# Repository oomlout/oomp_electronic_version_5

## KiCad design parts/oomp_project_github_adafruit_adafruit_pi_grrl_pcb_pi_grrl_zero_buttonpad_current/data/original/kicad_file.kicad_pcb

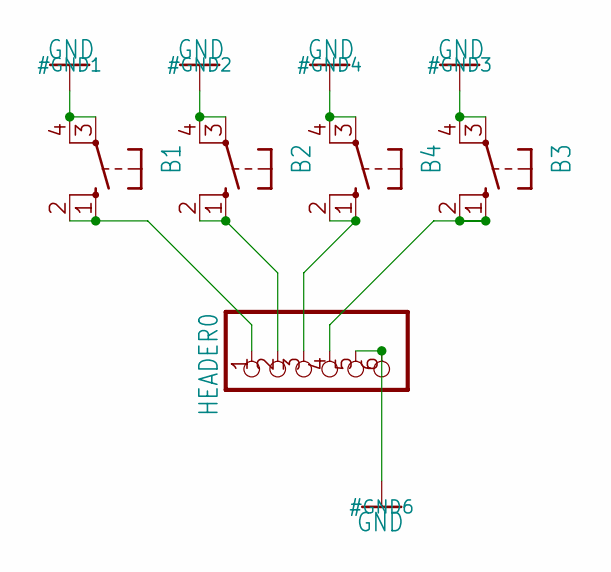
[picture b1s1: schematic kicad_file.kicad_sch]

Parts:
B1, B2, B3, B4: 10-XX; B3F-10XX; MPN B3F-1000
HEADER0: PINHD-1X6; 1X06

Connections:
GND: B1.3, B1.4 (P1), B2.3, B2.4 (P1), B3.3, B3.4 (P1), B4.3, B4.4 (P1), HEADER0.5, HEADER0.6
unnamed: B1.1 (S), B1.2 (S1), HEADER0.1
unnamed: B2.1 (S), B2.2 (S1), HEADER0.2
unnamed: B3.1 (S), B3.2 (S1), HEADER0.4
unnamed: B4.1 (S), B4.2 (S1), HEADER0.3

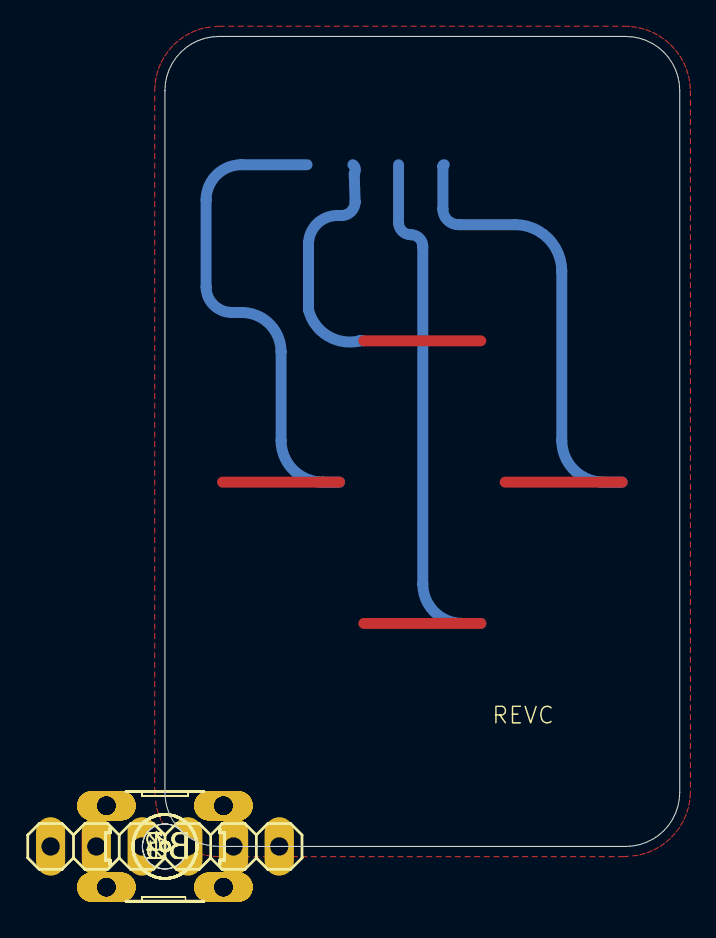
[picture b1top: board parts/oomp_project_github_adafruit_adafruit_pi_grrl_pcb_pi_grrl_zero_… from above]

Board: 16 copper layers, 28.6 x 45.0 mm, 7 parts (0 on the bottom side), 5 nets.

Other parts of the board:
UNK_HOLE_0: dummyfp0
UNK_HOLE_1: dummyfp1

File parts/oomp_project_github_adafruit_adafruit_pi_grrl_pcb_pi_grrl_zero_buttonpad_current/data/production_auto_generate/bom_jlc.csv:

Comment,Designator,Footprint,LCSC Part #
,HEADER0,PiGRRL_Zero_buttonpad-import-fps:1X06,C37208
,"B1,B2,B3,B4",PiGRRL_Zero_buttonpad-import-fps:B3F-10XX,

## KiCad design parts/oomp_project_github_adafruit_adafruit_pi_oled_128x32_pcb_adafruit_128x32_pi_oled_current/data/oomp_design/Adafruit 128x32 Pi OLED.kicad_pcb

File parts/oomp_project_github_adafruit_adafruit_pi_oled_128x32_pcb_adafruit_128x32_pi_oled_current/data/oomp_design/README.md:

# OOMP KiCad design copy

Open `Adafruit 128x32 Pi OLED.kicad_pro` (or the `.kicad_pcb` / `.kicad_sch`) in KiCad. Local OOMP libraries are under `libraries/`. Original inputs are preserved in [../original/](../original/).

Only verified unchanged installed KiCad defaults were renamed. Modified, custom, unmatched and unavailable items remain unchanged. Soldering variants are never swapped during conversion. Existing pad coordinates, nets and UUIDs are preserved.

See [conversion_report.yaml](conversion_report.yaml) for every conversion and skip. Copy this directory before editing; regeneration refuses to overwrite edited design files.

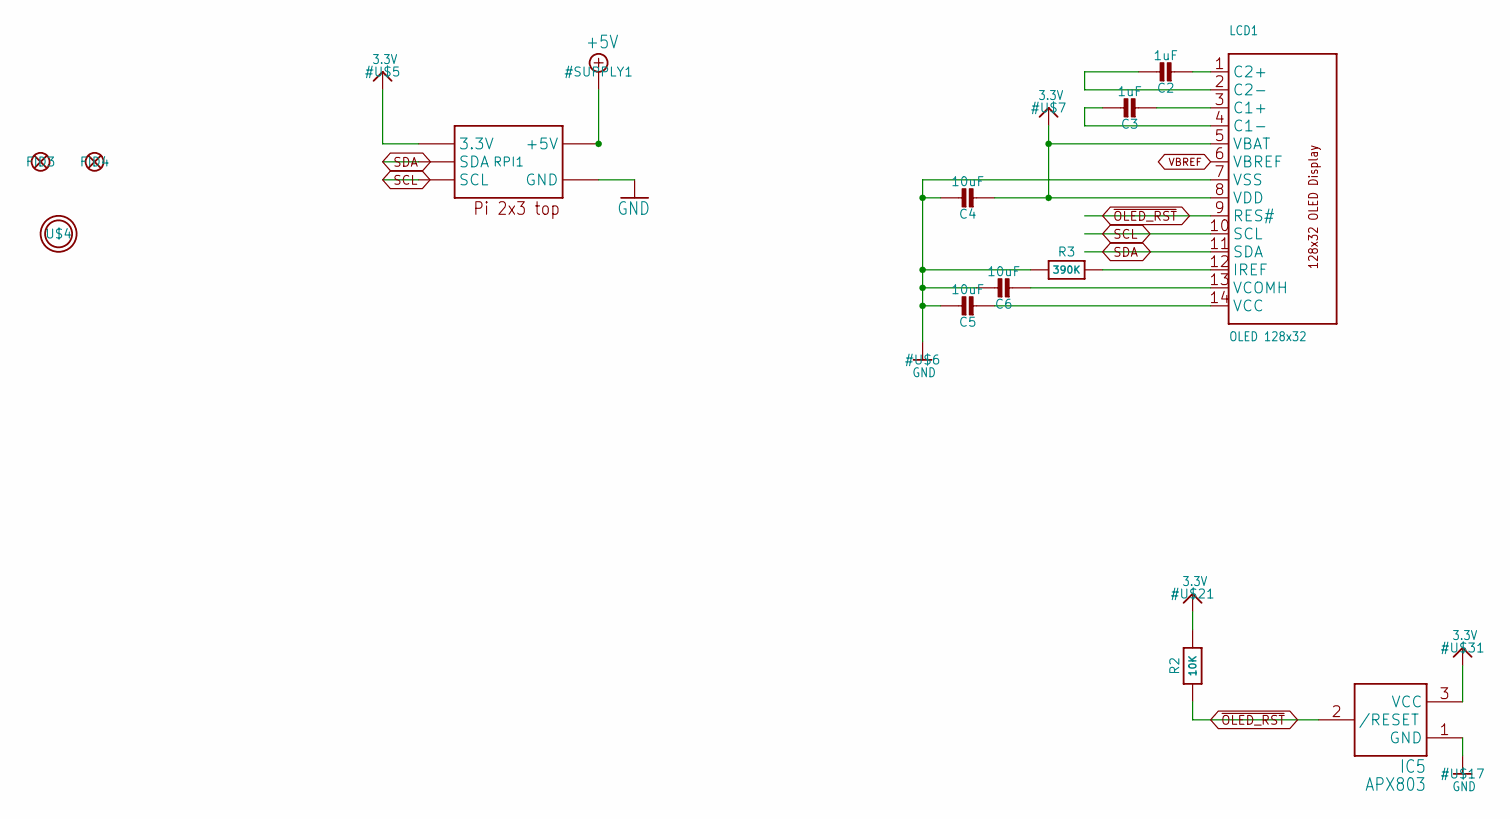
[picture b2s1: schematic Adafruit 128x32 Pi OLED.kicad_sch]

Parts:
C2, C3: 1uF; 0805-NO
C4, C5, C6: 10uF; 0805-NO
FID3, FID4: FIDUCIAL_1MM
IC5: APX803; SOT23
LCD1: OLED 128x32; UG-2832HSWEG02_WRAPUNDER
R2: 10K; 0805-NO
R3: 390K; 0805-NO
RPI1: RASPBERRYPI_2X3; RASPBERRYPI_2X3_THMSMT
U$4: MOUNTINGHOLE3.0THIN; MOUNTINGHOLE_3.0_PLATEDTHIN

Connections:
3.3V: C4.2, IC5.3 (VCC), LCD1.5 (VBAT), LCD1.8 (VDD), R2.2, RPI1.1 (3.3V), RPI1.1' (3.3V)
+5V: RPI1.2 (+5V), RPI1.2' (+5V), RPI1.4 (+5V), RPI1.4' (+5V)
GND: C4.1, C5.1, C6.1, IC5.1 (GND), LCD1.7 (VSS), R3.1, RPI1.6 (GND), RPI1.6' (GND)
unnamed: C2.2, LCD1.1 (C2+)
unnamed: C2.1, LCD1.2 (C2-)
unnamed: C3.2, LCD1.3 (C1+)
unnamed: C3.1, LCD1.4 (C1-)
unnamed: C6.2, LCD1.13 (VCOMH)
unnamed: C5.2, LCD1.14 (VCC)
unnamed: LCD1.12 (IREF), R3.2
SCL: LCD1.10 (SCL), RPI1.5 (SCL), RPI1.5' (SCL)
SDA: LCD1.11 (SDA), RPI1.3 (SDA), RPI1.3' (SDA)
VBREF: LCD1.6 (VBREF)
~OLED_RST: IC5.2 (/RESET), LCD1.9 (RES#), R2.1

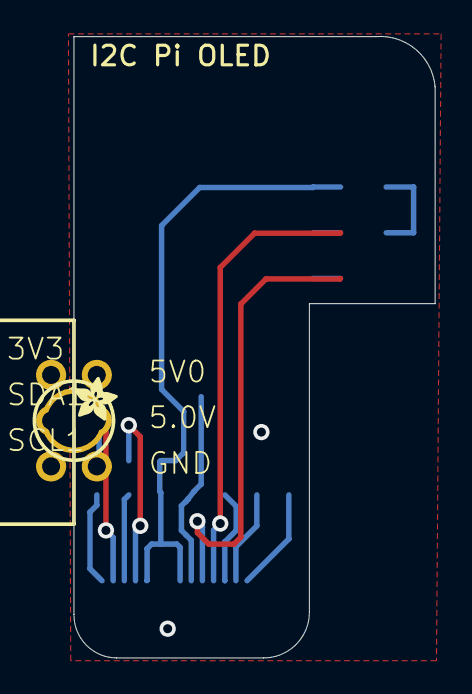
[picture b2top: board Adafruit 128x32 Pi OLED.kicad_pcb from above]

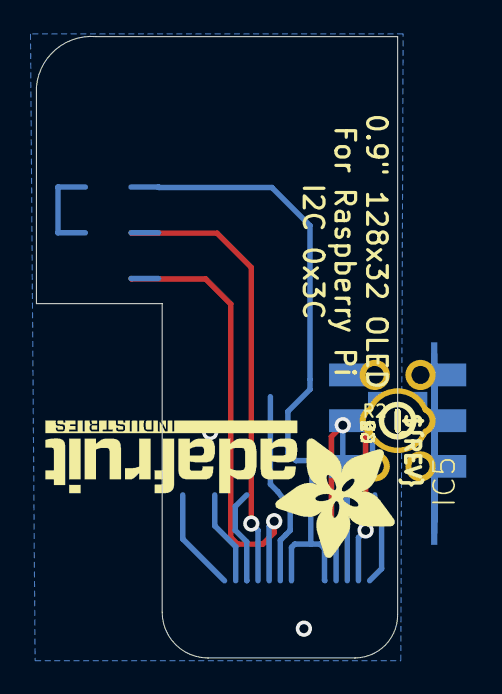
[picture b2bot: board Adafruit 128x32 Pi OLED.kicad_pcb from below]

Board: 16 copper layers, 20.1 x 34.5 mm, 16 parts (12 on the bottom side), 13 nets.

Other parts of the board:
U$1: ADAFRUIT_2.5MM
U$3: PCBFEAT-REV-040
U$8: ADAFRUIT_TEXT_20MM

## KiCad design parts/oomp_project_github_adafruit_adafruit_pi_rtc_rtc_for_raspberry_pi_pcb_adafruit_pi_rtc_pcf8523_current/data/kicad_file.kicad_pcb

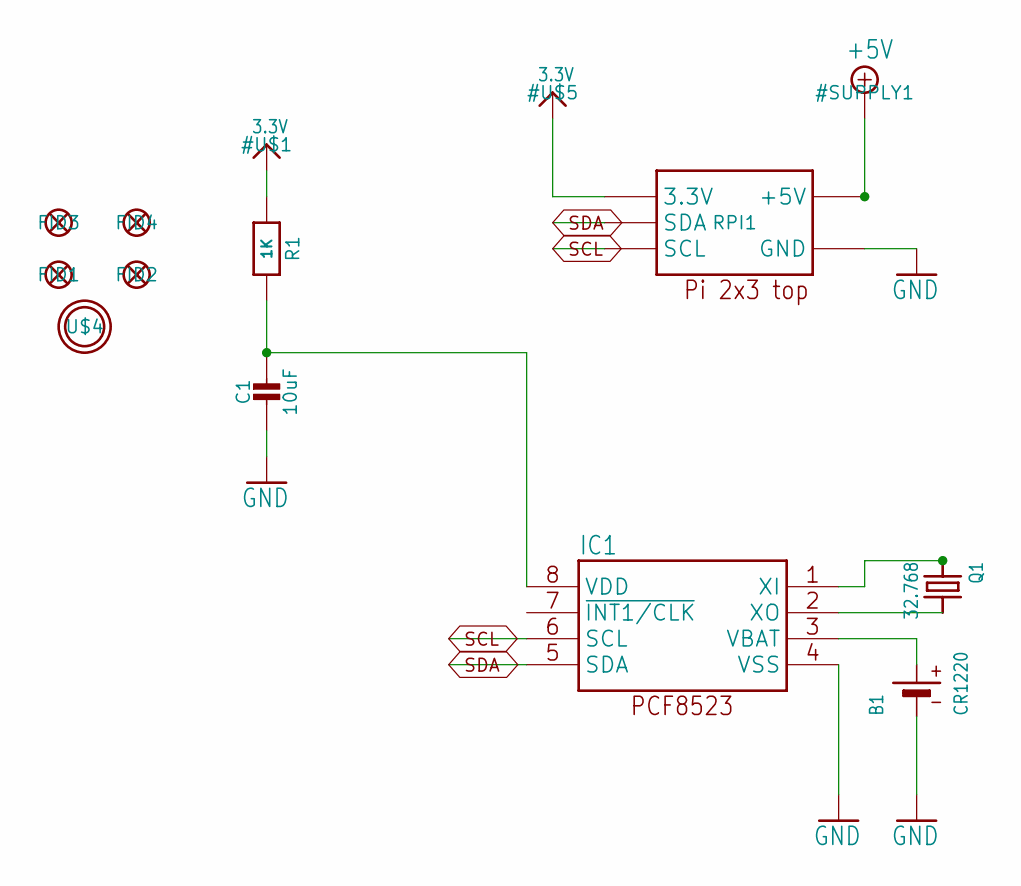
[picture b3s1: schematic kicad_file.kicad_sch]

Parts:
B1: CR1220
C1: 10uF; 0805-NO
FID1, FID2, FID3, FID4: FIDUCIAL_1MM
IC1: RTC_PCF8523T; SOIC8_150MIL
Q1: 32.768; CRYSTAL_8X3.8
R1: 1K; 0805-NO
RPI1: RASPBERRYPI_2X3; RASPBERRYPI_2X3_THMSMT
U$4: MOUNTINGHOLE3.0THIN; MOUNTINGHOLE_3.0_PLATEDTHIN

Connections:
3.3V: R1.1, RPI1.1 (3.3V), RPI1.1' (3.3V)
+5V: RPI1.2 (+5V), RPI1.2' (+5V), RPI1.4 (+5V), RPI1.4' (+5V)
GND: B1.-, C1.2, IC1.4 (VSS), RPI1.6 (GND), RPI1.6' (GND)
unnamed: IC1.1 (XI), Q1.P$1 (1)
unnamed: IC1.2 (XO), Q1.P$4 (2)
SCL: IC1.6 (SCL), RPI1.5 (SCL), RPI1.5' (SCL)
SDA: IC1.5 (SDA), RPI1.3 (SDA), RPI1.3' (SDA)
VBAT: B1.+$1 (+), B1.+$2 (+), IC1.3 (VBAT)
VDD: C1.1, IC1.8 (VDD), R1.2

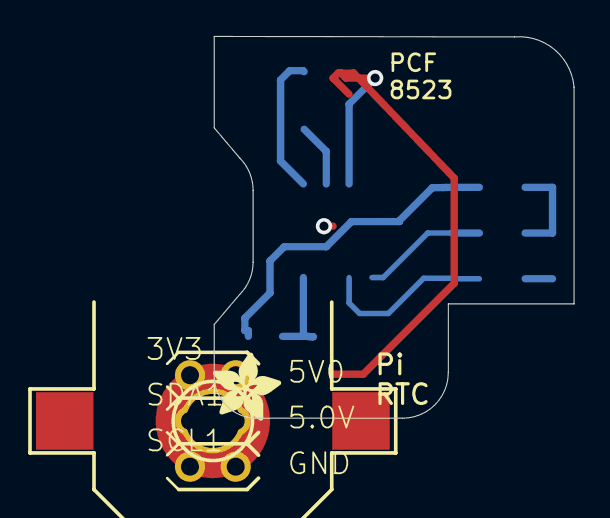
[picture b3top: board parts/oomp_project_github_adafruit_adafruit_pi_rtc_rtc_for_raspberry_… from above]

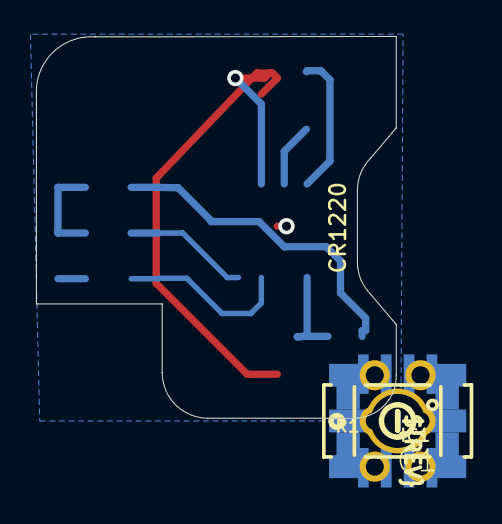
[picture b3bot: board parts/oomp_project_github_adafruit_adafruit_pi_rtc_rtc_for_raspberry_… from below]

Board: 16 copper layers, 20.0 x 21.2 mm, 13 parts (7 on the bottom side), 9 nets.

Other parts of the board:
U$2: ADAFRUIT_3.5MM
U$3: PCBFEAT-REV-040

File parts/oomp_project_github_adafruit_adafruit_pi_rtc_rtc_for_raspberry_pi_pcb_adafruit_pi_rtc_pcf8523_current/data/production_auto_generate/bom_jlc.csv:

Comment,Designator,Footprint,LCSC Part #
,U$2,Adafruit PiRTC PCF8523-import-fps:ADAFRUIT_3.5MM,
,U$3,Adafruit PiRTC PCF8523-import-fps:PCBFEAT-REV-040,
10uF,C1,Adafruit PiRTC PCF8523-import-fps:0805-NO,
1K,R1,Adafruit PiRTC PCF8523-import-fps:0805-NO,C17513
32.768,Q1,Adafruit PiRTC PCF8523-import-fps:CRYSTAL_8X3.8,
CR1220,B1,Adafruit PiRTC PCF8523-import-fps:CR1220,
RASPBERRYPI_2X3,RPI1,Adafruit PiRTC PCF8523-import-fps:RASPBERRYPI_2X3_THMSMT,
RTC_PCF8523T,IC1,Adafruit PiRTC PCF8523-import-fps:SOIC8_150MIL,

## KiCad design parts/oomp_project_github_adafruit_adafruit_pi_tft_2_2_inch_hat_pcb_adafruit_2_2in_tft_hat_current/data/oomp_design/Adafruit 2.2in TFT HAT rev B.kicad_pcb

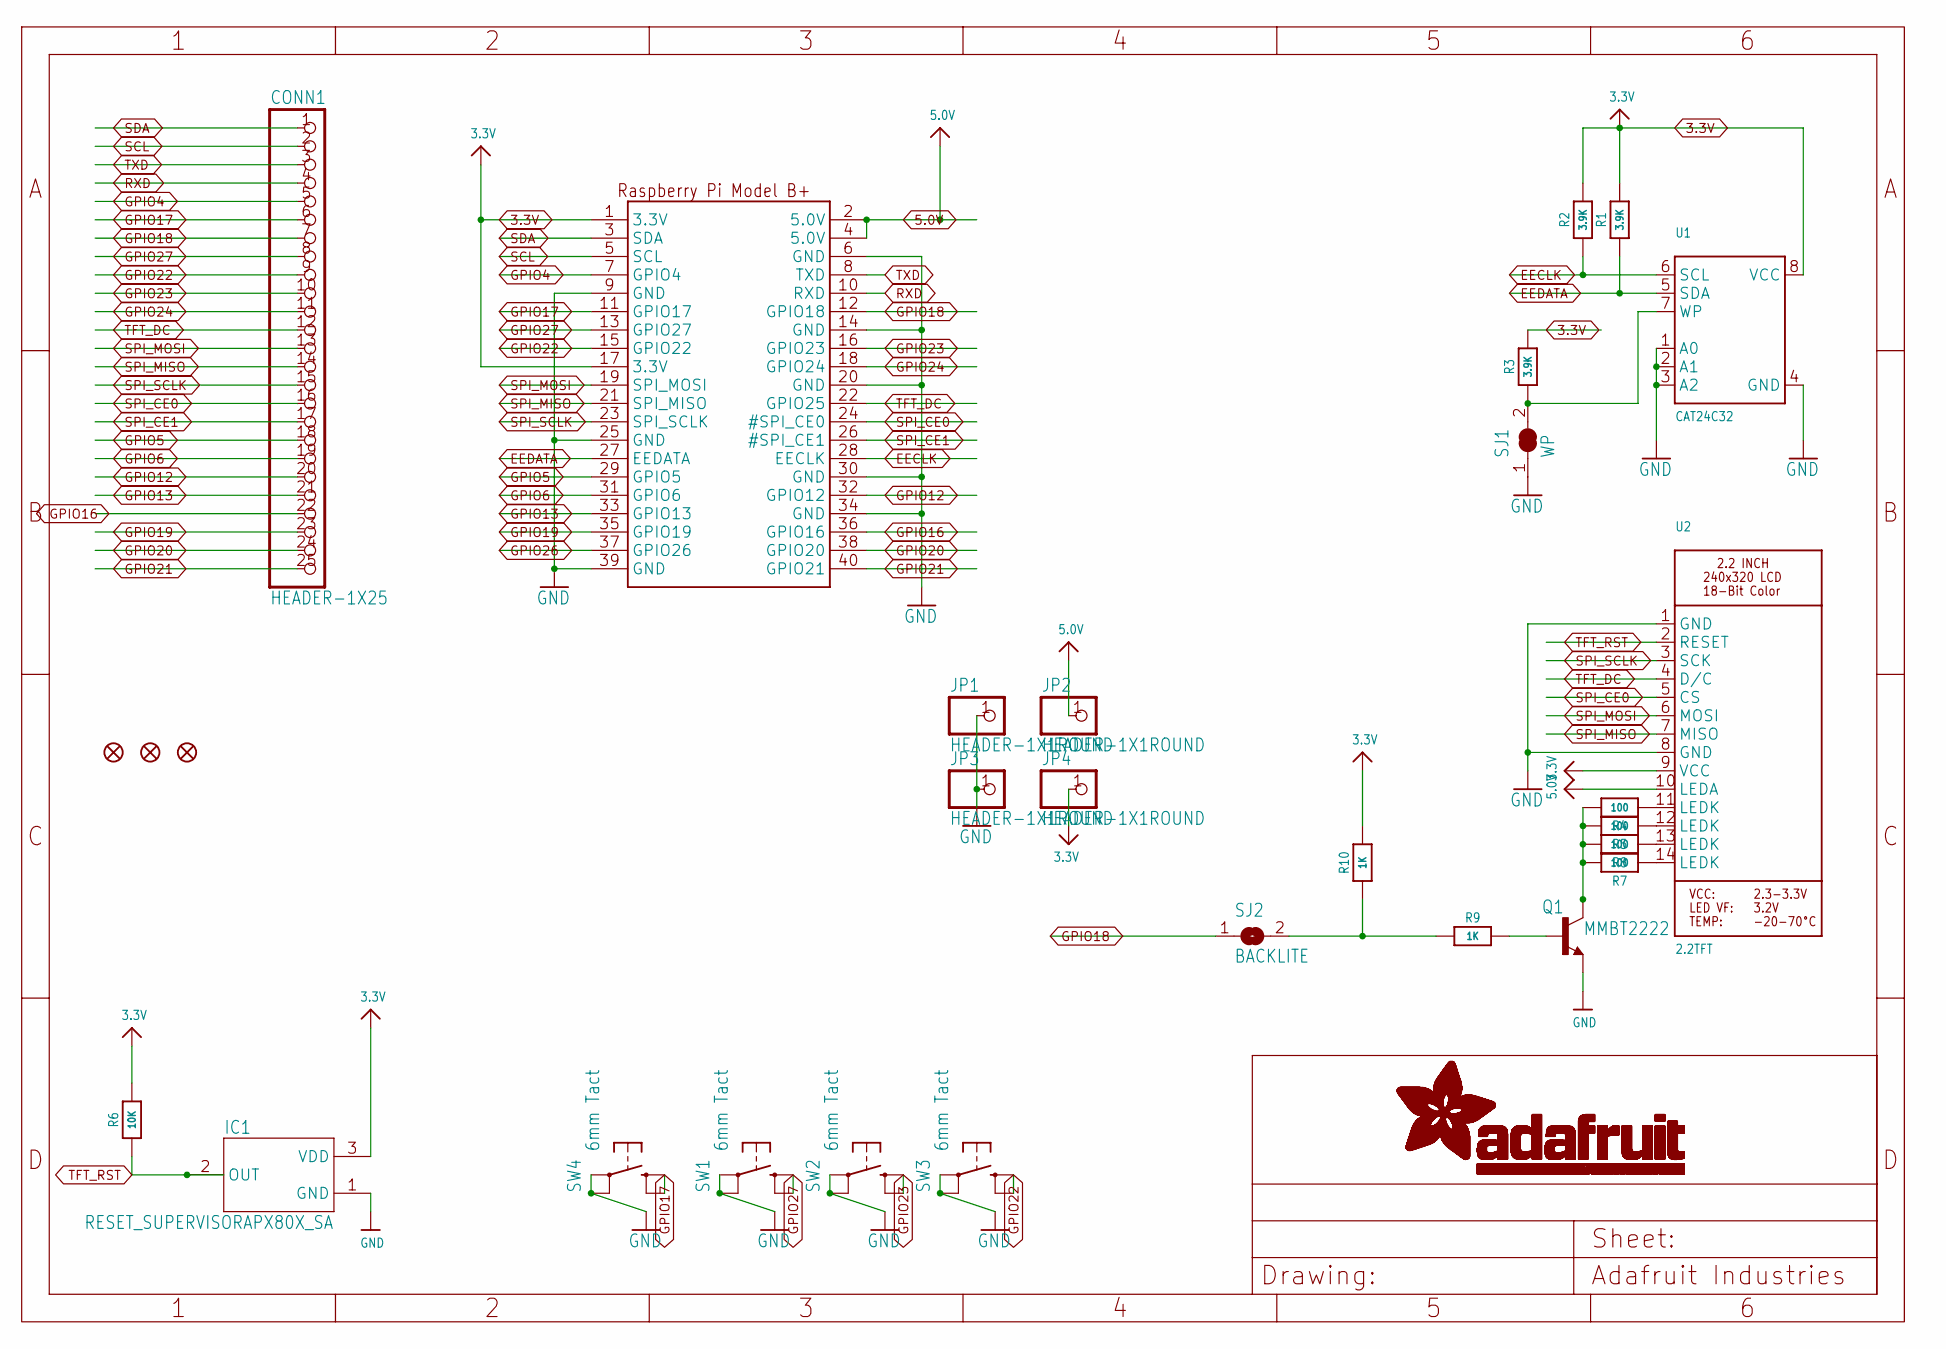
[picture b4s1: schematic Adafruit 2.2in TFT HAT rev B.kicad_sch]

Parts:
CONN1: HEADER-1X25; 1X25_ROUND_70MIL
FID1, FID2, FID3: FIDUCIAL_1MM
IC1: RESET_SUPERVISORAPX80X_SA; SOT23-WIDE
JP1, JP2, JP3, JP4: HEADER-1X1ROUND; 1X01_ROUND
Q1: MMBT2222; SOT23-BEC
R1, R2, R3: 3.9K; 0805-NO
R4, R5, R7, R8: 100; 0805-NO
R6: 10K; 0805-NO
R9, R10: 1K; 0805-NO
RPI1: RASPBERRYPI_BPLUS_HATNODIM; PI_HAT_NODIM
SJ1: WP; SOLDERJUMPER_CLOSEDWIRE
SJ2: BACKLITE; SOLDERJUMPER_CLOSEDWIRE
SW1, SW2, SW3, SW4: 6mm Tact; EVQ-Q2
U1: CAT24C32; SOIC8_150MIL
U2: 2.2TFT; TM022HDH26_2.2IN_LCD

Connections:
3.3V: IC1.3 (VDD), JP4.1, R1.2, R2.2, R3.2, R6.2, R10.2, RPI1.1 (3.3V), RPI1.17 (3.3V), U1.8 (VCC), U2.9 (VCC)
5.0V: JP2.1, RPI1.2 (5.0V), RPI1.4 (5.0V), U2.10 (LEDA)
EECLK: R2.1, RPI1.28 (EECLK), U1.6 (SCL)
EEDATA: R1.1, RPI1.27 (EEDATA), U1.5 (SDA)
GND: IC1.1 (GND), JP1.1, JP3.1, Q1.E, RPI1.6 (GND), RPI1.9 (GND), RPI1.14 (GND), RPI1.20 (GND), RPI1.25 (GND), RPI1.30 (GND), RPI1.34 (GND), RPI1.39 (GND), SJ1.1, SW1.A, SW1.A' (P1), SW2.A, SW2.A' (P1), SW3.A, SW3.A' (P1), SW4.A, SW4.A' (P1), U1.1 (A0), U1.2 (A1), U1.3 (A2), U1.4 (GND), U2.1 (GND), U2.8 (GND)
GPIO4: CONN1.5, RPI1.7 (GPIO4)
GPIO5: CONN1.18, RPI1.29 (GPIO5)
GPIO6: CONN1.19, RPI1.31 (GPIO6)
GPIO12: CONN1.20, RPI1.32 (GPIO12)
GPIO13: CONN1.21, RPI1.33 (GPIO13)
GPIO16: CONN1.22, RPI1.36 (GPIO16)
GPIO17: CONN1.6, RPI1.11 (GPIO17), SW4.B (S), SW4.B' (S1)
GPIO18: CONN1.7, RPI1.12 (GPIO18), SJ2.1
GPIO19: CONN1.23, RPI1.35 (GPIO19)
GPIO20: CONN1.24, RPI1.38 (GPIO20)
GPIO21: CONN1.25, RPI1.40 (GPIO21)
GPIO22: CONN1.9, RPI1.15 (GPIO22), SW3.B (S), SW3.B' (S1)
GPIO23: CONN1.10, RPI1.16 (GPIO23), SW2.B (S), SW2.B' (S1)
GPIO24: CONN1.11, RPI1.18 (GPIO24)
GPIO26: RPI1.37 (GPIO26)
GPIO27: CONN1.8, RPI1.13 (GPIO27), SW1.B (S), SW1.B' (S1)
unnamed: R4.1, U2.11 (LEDK)
unnamed: R5.1, U2.12 (LEDK)
unnamed: R7.1, U2.14 (LEDK)
unnamed: R8.1, U2.13 (LEDK)
unnamed: Q1.C, R4.2, R5.2, R7.2, R8.2
unnamed: Q1.B, R9.2
unnamed: R9.1, R10.1, SJ2.2
unnamed: R3.1, SJ1.2, U1.7 (WP)
RXD: CONN1.4, RPI1.10 (RXD)
SCL: CONN1.2, RPI1.5 (SCL)
SDA: CONN1.1, RPI1.3 (SDA)
SPI_CE0: CONN1.16, RPI1.24 (#SPI_CE0), U2.5 (CS)
SPI_CE1: CONN1.17, RPI1.26 (#SPI_CE1)
SPI_MISO: CONN1.14, RPI1.21 (SPI_MISO), U2.7 (MISO)
SPI_MOSI: CONN1.13, RPI1.19 (SPI_MOSI), U2.6 (MOSI)
SPI_SCLK: CONN1.15, RPI1.23 (SPI_SCLK), U2.3 (SCK)
TFT_DC: CONN1.12, RPI1.22 (GPIO25), U2.4 (D/C)
TFT_RST: IC1.2 (OUT), R6.1, U2.2 (RESET)
TXD: CONN1.3, RPI1.8 (TXD)

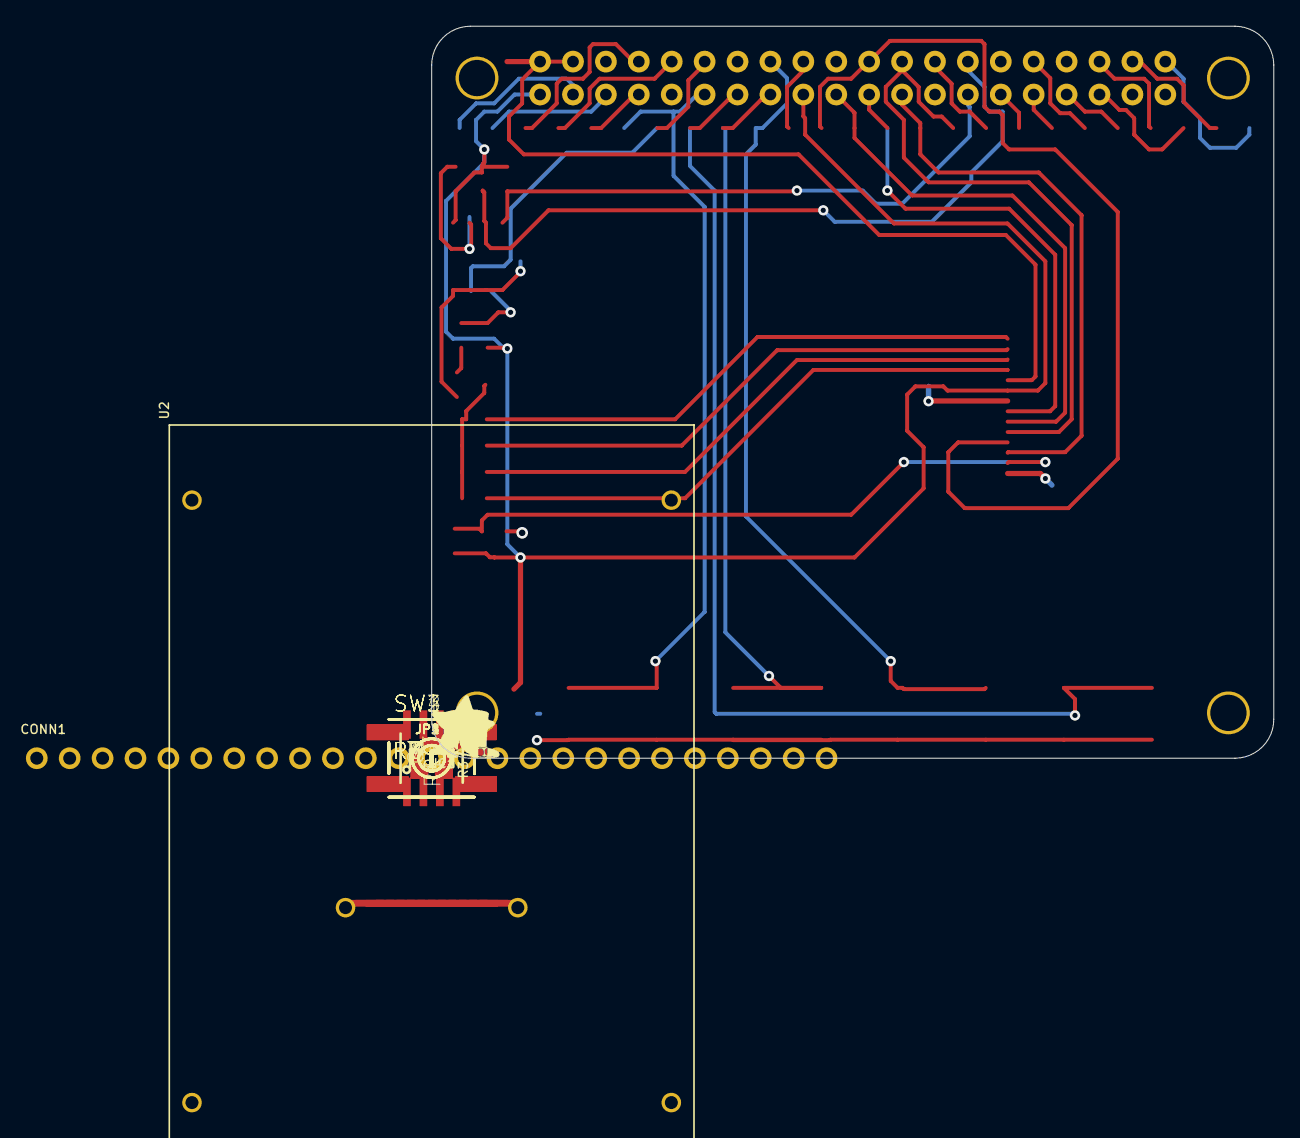
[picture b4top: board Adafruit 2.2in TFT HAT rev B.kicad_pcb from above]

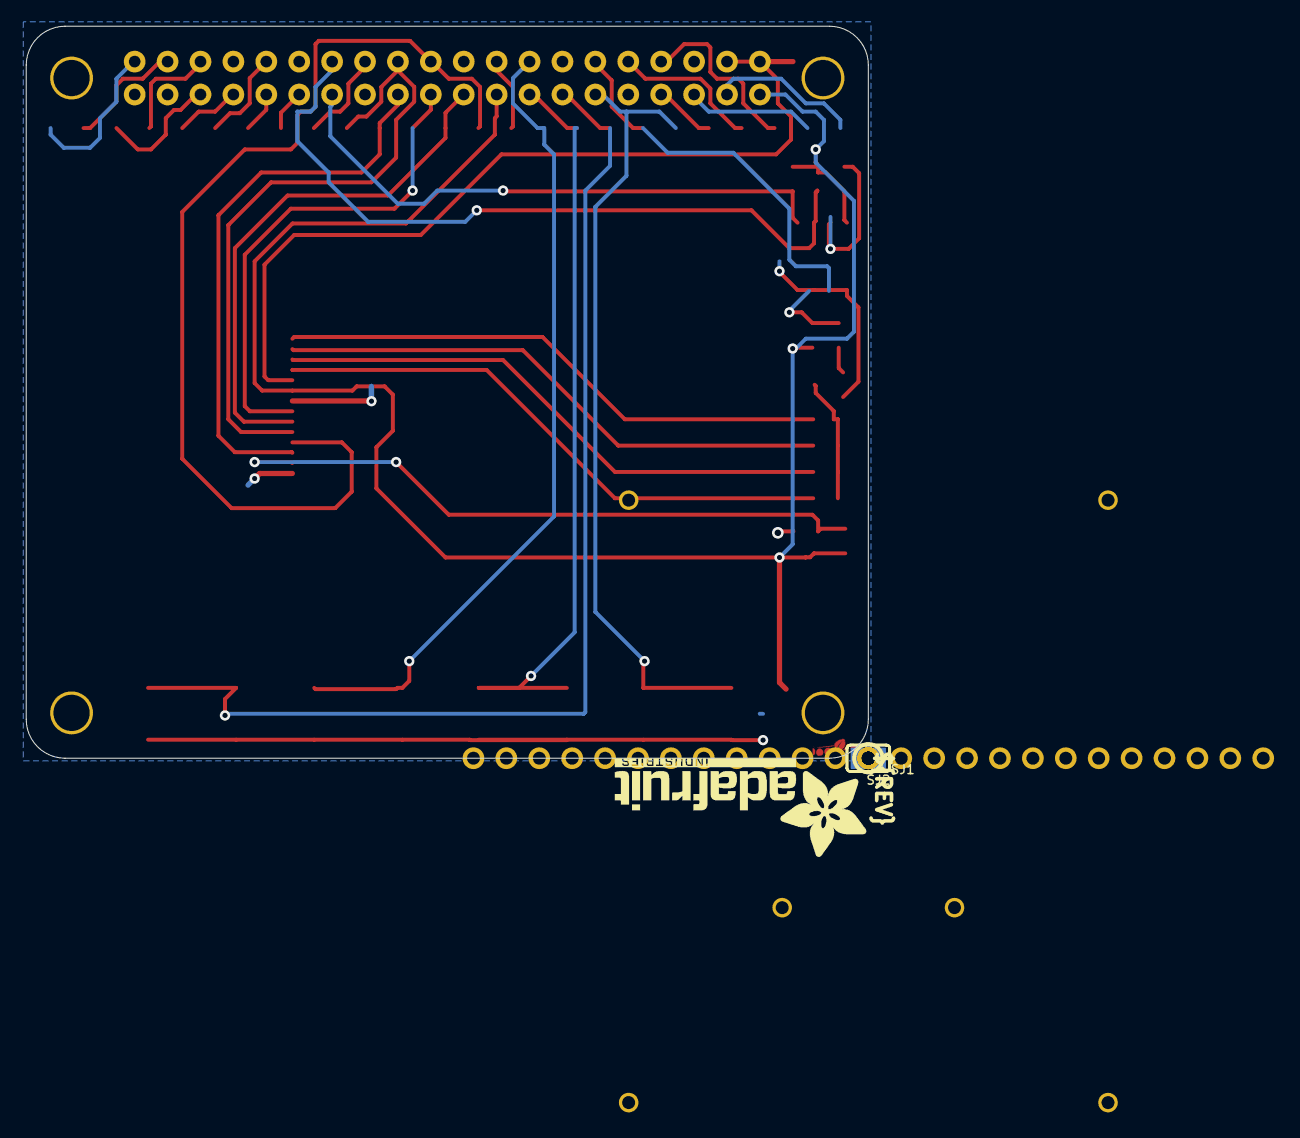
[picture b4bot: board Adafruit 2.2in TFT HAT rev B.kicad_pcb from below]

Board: 2 copper layers, 65.0 x 56.5 mm, 69 parts (6 on the bottom side), 39 nets.

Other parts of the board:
PLABEL0: PLABEL0
PLABEL1: PLABEL1
PLABEL2: PLABEL2
PLABEL3: PLABEL3
PLABEL4: PLABEL4
PLABEL5: PLABEL5
PLABEL6: PLABEL6
PLABEL7: PLABEL7
PLABEL8: PLABEL8
PLABEL9: PLABEL9
PLABEL10: PLABEL10
PLABEL11: PLABEL11
PLABEL12: PLABEL12
PLABEL13: PLABEL13
PLABEL14: PLABEL14
PLABEL15: PLABEL15
PLABEL16: PLABEL16
PLABEL17: PLABEL17
PLABEL18: PLABEL18
PLABEL19: PLABEL19
PLABEL20: PLABEL20
PLABEL21: PLABEL21
PLABEL22: PLABEL22
PLABEL23: PLABEL23
PLABEL24: PLABEL24
PLABEL25: PLABEL25
PLABEL26: PLABEL26
PLABEL27: PLABEL27
PLABEL28: PLABEL28
PLABEL29: PLABEL29
PLABEL30: PLABEL30
PLABEL31: PLABEL31
PLABEL32: PLABEL32
PLABEL33: PLABEL33
PLABEL34: PLABEL34
PLABEL35: PLABEL35
U$1: ADAFRUIT_5MM
U$3: ADAFRUIT_TEXT_20MM
U$4: PIHATLOGO
U$12: PCBFEAT-REV-056

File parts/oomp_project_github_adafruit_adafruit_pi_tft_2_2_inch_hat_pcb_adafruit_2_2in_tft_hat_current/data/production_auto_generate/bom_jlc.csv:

Comment,Designator,Footprint,LCSC Part #
,"JP1,JP2,JP3,JP4",Adafruit 2.2in TFT HAT rev B-import-fps:1X01_ROUND,C7501259
,U$1,Adafruit 2.2in TFT HAT rev B-import-fps:ADAFRUIT_5MM,
,U$3,Adafruit 2.2in TFT HAT rev B-import-fps:ADAFRUIT_TEXT_20MM,
,U$12,Adafruit 2.2in TFT HAT rev B-import-fps:PCBFEAT-REV-056,
,U$4,Adafruit 2.2in TFT HAT rev B-import-fps:PIHATLOGO,
,PLABEL0,Adafruit 2.2in TFT HAT rev B-import-fps:PLABEL0,
,PLABEL1,Adafruit 2.2in TFT HAT rev B-import-fps:PLABEL1,
,PLABEL10,Adafruit 2.2in TFT HAT rev B-import-fps:PLABEL10,
,PLABEL11,Adafruit 2.2in TFT HAT rev B-import-fps:PLABEL11,
,PLABEL12,Adafruit 2.2in TFT HAT rev B-import-fps:PLABEL12,
,PLABEL13,Adafruit 2.2in TFT HAT rev B-import-fps:PLABEL13,
,PLABEL14,Adafruit 2.2in TFT HAT rev B-import-fps:PLABEL14,
,PLABEL15,Adafruit 2.2in TFT HAT rev B-import-fps:PLABEL15,
,PLABEL16,Adafruit 2.2in TFT HAT rev B-import-fps:PLABEL16,
,PLABEL17,Adafruit 2.2in TFT HAT rev B-import-fps:PLABEL17,
,PLABEL18,Adafruit 2.2in TFT HAT rev B-import-fps:PLABEL18,
,PLABEL19,Adafruit 2.2in TFT HAT rev B-import-fps:PLABEL19,
,PLABEL2,Adafruit 2.2in TFT HAT rev B-import-fps:PLABEL2,
,PLABEL20,Adafruit 2.2in TFT HAT rev B-import-fps:PLABEL20,
,PLABEL21,Adafruit 2.2in TFT HAT rev B-import-fps:PLABEL21,
,PLABEL22,Adafruit 2.2in TFT HAT rev B-import-fps:PLABEL22,
,PLABEL23,Adafruit 2.2in TFT HAT rev B-import-fps:PLABEL23,
,PLABEL24,Adafruit 2.2in TFT HAT rev B-import-fps:PLABEL24,
,PLABEL25,Adafruit 2.2in TFT HAT rev B-import-fps:PLABEL25,
,PLABEL26,Adafruit 2.2in TFT HAT rev B-import-fps:PLABEL26,
,PLABEL27,Adafruit 2.2in TFT HAT rev B-import-fps:PLABEL27,
,PLABEL28,Adafruit 2.2in TFT HAT rev B-import-fps:PLABEL28,
,PLABEL29,Adafruit 2.2in TFT HAT rev B-import-fps:PLABEL29,
,PLABEL3,Adafruit 2.2in TFT HAT rev B-import-fps:PLABEL3,
,PLABEL30,Adafruit 2.2in TFT HAT rev B-import-fps:PLABEL30,
,PLABEL31,Adafruit 2.2in TFT HAT rev B-import-fps:PLABEL31,
,PLABEL32,Adafruit 2.2in TFT HAT rev B-import-fps:PLABEL32,
,PLABEL33,Adafruit 2.2in TFT HAT rev B-import-fps:PLABEL33,
,PLABEL34,Adafruit 2.2in TFT HAT rev B-import-fps:PLABEL34,
,PLABEL35,Adafruit 2.2in TFT HAT rev B-import-fps:PLABEL35,
,PLABEL4,Adafruit 2.2in TFT HAT rev B-import-fps:PLABEL4,
,PLABEL5,Adafruit 2.2in TFT HAT rev B-import-fps:PLABEL5,
,PLABEL6,Adafruit 2.2in TFT HAT rev B-import-fps:PLABEL6,
,PLABEL7,Adafruit 2.2in TFT HAT rev B-import-fps:PLABEL7,
,PLABEL8,Adafruit 2.2in TFT HAT rev B-import-fps:PLABEL8,
,PLABEL9,Adafruit 2.2in TFT HAT rev B-import-fps:PLABEL9,
100,"R4,R5,R7,R8",Adafruit 2.2in TFT HAT rev B-import-fps:0805-NO,C17408
10K,R6,Adafruit 2.2in TFT HAT rev B-import-fps:0805-NO,C17414
1K,"R9,R10",Adafruit 2.2in TFT HAT rev B-import-fps:0805-NO,C17513
2.2TFT,U2,Adafruit 2.2in TFT HAT rev B-import-fps:TM022HDH26_2.2IN_LCD,
3.9K,"R1,R2,R3",Adafruit 2.2in TFT HAT rev B-import-fps:0805-NO,C2907252
6mm Tact,"SW1,SW2,SW3,SW4",Adafruit 2.2in TFT HAT rev B-import-fps:EVQ-Q2,
CAT24C32,U1,Adafruit 2.2in TFT HAT rev B-import-fps:SOIC8_150MIL,
HEADER-1X25,CONN1,Adafruit 2.2in TFT HAT rev B-import-fps:1X25_ROUND_70MIL,C2883713
MMBT2222,Q1,Adafruit 2.2in TFT HAT rev B-import-fps:SOT23-BEC,
RASPBERRYPI_BPLUS_HATNODIM,RPI1,Adafruit 2.2in TFT HAT rev B-import-fps:PI_HAT_NODIM,
RESET_SUPERVISORAPX80X_SA,IC1,Adafruit 2.2in TFT HAT rev B-import-fps:SOT23-WIDE,

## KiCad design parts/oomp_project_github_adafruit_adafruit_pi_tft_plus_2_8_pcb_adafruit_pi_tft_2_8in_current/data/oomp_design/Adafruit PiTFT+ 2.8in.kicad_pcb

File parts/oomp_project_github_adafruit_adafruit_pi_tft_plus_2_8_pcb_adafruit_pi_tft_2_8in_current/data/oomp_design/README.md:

# OOMP KiCad design copy

Open `Adafruit PiTFT+ 2.8in.kicad_pro` (or the `.kicad_pcb` / `.kicad_sch`) in KiCad. Local OOMP libraries are under `libraries/`. Original inputs are preserved in [../original/](../original/).

Only verified unchanged installed KiCad defaults were renamed. Modified, custom, unmatched and unavailable items remain unchanged. Soldering variants are never swapped during conversion. Existing pad coordinates, nets and UUIDs are preserved.

See [conversion_report.yaml](conversion_report.yaml) for every conversion and skip. Copy this directory before editing; regeneration refuses to overwrite edited design files.

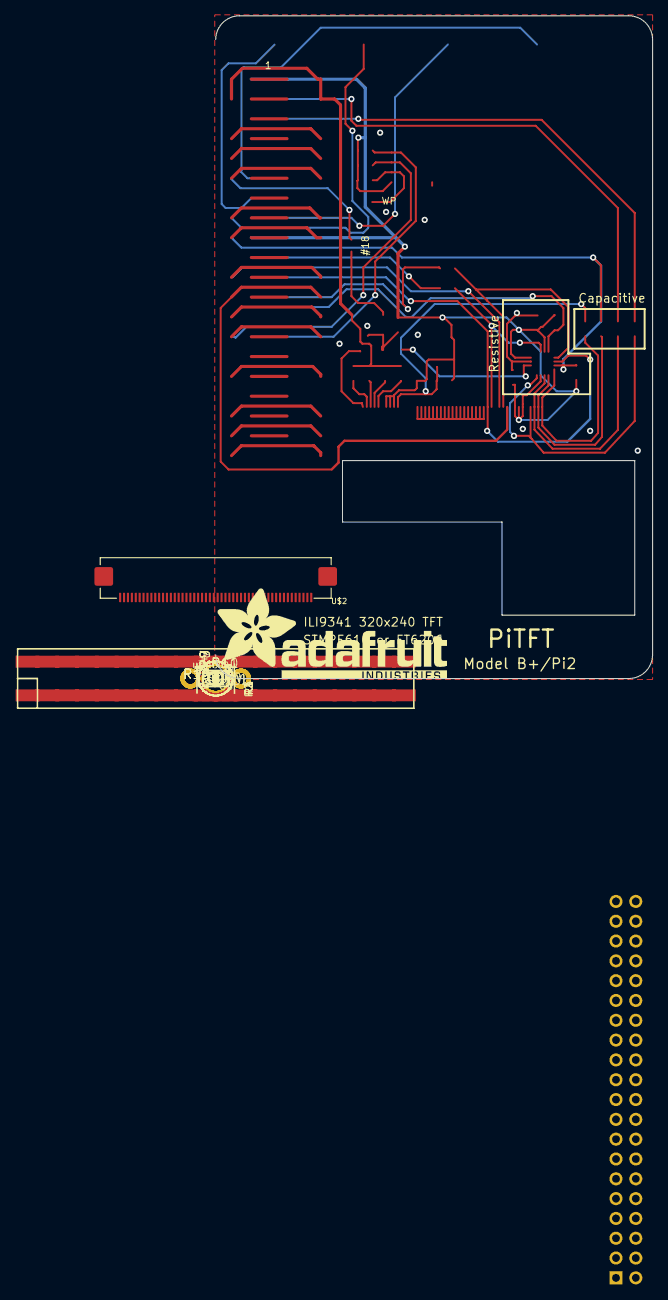
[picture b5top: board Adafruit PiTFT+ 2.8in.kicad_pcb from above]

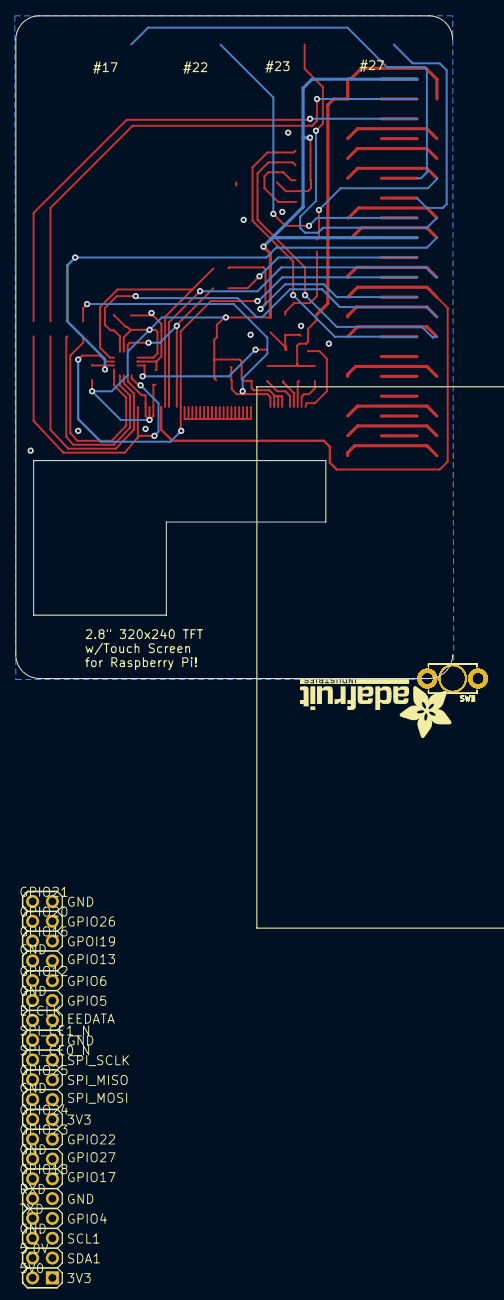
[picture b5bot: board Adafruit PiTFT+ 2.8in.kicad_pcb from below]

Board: 16 copper layers, 56.0 x 85.0 mm, 48 parts (7 on the bottom side), 48 nets.

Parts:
C1, C5: 10uF; 0805-NO
C2, C3, C4: 0.1uF; 0805-NO
D1, D2: 1N4148; SOD-323
IC5: APX803; SOT23
JP3: 2X20_SMT_MALE
Q2: BSS138; SOT23-WIDE
R1, R2, R3, R4: 100; 0805-NO
R6, R7: 10K; 0805-NO
R8: DNP; 0805-NO
R9, R12, R13, R14: 3.9K; 0805-NO
R10, R11: 22; 0805-NO
R15, R16, R17, R18: 0; 0805-NO
RPI1: RASPBERRYPI_BPLUS_SHIELD_NODIM
SW1, SW2, SW3, SW4: TACT_PANA-EVQ
U1: CAT24C32; SOIC8_150MIL
U2: STMPE811; QFN16_3MM
U$2: DISP_LCD_240X320_50PIN_2.8IN; TFT_2.83IN_240X320_50PIN
U$3, U$15, U$16, U$17, U$40: MOUNTINGHOLE3.0THIN; MOUNTINGHOLE_3.0_PLATEDTHIN
U$10, U$11, U$18: FIDUCIAL""; FIDUCIAL_1MM
U$12: PCBFEAT-REV-040
U$23: ADAFRUIT_TEXT_20MM
U$42: ADAFRUIT_TEXT_30MM
WPJ0, WPJ1: SOLDERJUMPER_CLOSEDWIRE

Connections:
3.3V: C1.1, C2.1, C3.1, C4.1, IC5.3, JP3.1, JP3.17, R6.2, R7.2, R8.1, R9.2, R12.2, R13.2, R14.2, RPI1.1, RPI1.17, U1.8, U2.6, U2.9, U2.14, U$2.7, U$2.8, U$2.9, U$2.40, U$2.41, U$2.42
+5V: C5.1, JP3.2, JP3.4, R1.1, R2.1, R3.1, R4.1, RPI1.2, RPI1.4
EECLK: JP3.28, R14.1, RPI1.28, U1.6
EEDATA: JP3.27, R13.1, RPI1.27, U1.5
GND: C1.2, C2.2, C3.2, C4.2, C5.2, IC5.1, JP3.6, JP3.9, JP3.14, JP3.20, JP3.25, JP3.30, JP3.34, JP3.39, Q2.2, RPI1.6, RPI1.9, RPI1.14, RPI1.20, RPI1.25, RPI1.30, RPI1.34, RPI1.39, SW1.P$2, SW2.P$2, SW3.P$2, SW4.P$2, U1.1, U1.2, U1.3, U1.4, U2.10, U$2.6, U$2.43, U$2.48, U$2.49, U$2.50, WPJ0.1
GPIO4: JP3.7, RPI1.7
GPIO5: JP3.29, RPI1.29
GPIO6: JP3.31, RPI1.31
GPIO12: JP3.32, RPI1.32
GPIO13: JP3.33, RPI1.33
GPIO16: JP3.36, RPI1.36
GPIO17: JP3.11, RPI1.11, SW3.P$1
GPIO18: JP3.12, RPI1.12, WPJ1.1
GPIO19: JP3.35, RPI1.35
GPIO20: JP3.38, RPI1.38
GPIO21: JP3.40, RPI1.40
GPIO22: JP3.15, RPI1.15, SW1.P$1
GPIO23: JP3.16, RPI1.16, SW4.P$1
GPIO26: JP3.37, RPI1.37
GPIO27: JP3.13, RPI1.13, SW2.P$1
MISO: JP3.21, RPI1.21, U2.3, U$2.33
MOSI: R11.2, U2.7, U$2.34
MOSI_3V: JP3.19, R11.1, RPI1.19
unnamed: Q2.3, U$2.1
unnamed: R1.2, U$2.2
unnamed: R2.2, U$2.3
unnamed: R3.2, U$2.4
unnamed: D1.C, U2.11
unnamed: D2.C, WPJ1.2
unnamed: U$2.15, U$2.16, U$2.17, U$2.18, U$2.19, U$2.20, U$2.21, U$2.22, U$2.23, U$2.24, U$2.25, U$2.26, U$2.27, U$2.28, U$2.29, U$2.30, U$2.31, U$2.32
unnamed: R4.2, U$2.5
unnamed: R12.1, U1.7, WPJ0.2
unnamed: D1.A, D2.A, Q2.1, R9.1
RT_CS_3V: JP3.26, R7.1, RPI1.26, U2.5
RT_INT: JP3.18, R8.2, R18.2, RPI1.18, U2.2
RXD: JP3.10, RPI1.10
SCL: JP3.5, R17.2, RPI1.5
SCLK: R10.2, U2.4, U$2.37
SCLK_3V: JP3.23, R10.1, RPI1.23
SDA: JP3.3, R16.2, RPI1.3
TFT_CS_3V: JP3.24, RPI1.24, U$2.38
TFT_DC_3V: JP3.22, RPI1.22, U$2.36
TFT_RST: IC5.2, R6.1, R15.2, U$2.10
TXD: JP3.8, RPI1.8
XL_CTPIRQ: R18.1, U2.16, U$2.46
XR_CTPSCL: R17.1, U2.13, U$2.44
YD_CTPSDA: R16.1, U2.15, U$2.45
YU_CTPRST: R15.1, U2.1, U$2.47

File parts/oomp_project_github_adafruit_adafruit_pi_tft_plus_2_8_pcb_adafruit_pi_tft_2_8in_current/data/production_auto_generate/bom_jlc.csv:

Comment,Designator,Footprint,LCSC Part #
,JP3,Adafruit PiTFT+ 2.8in-import-fps:2X20_SMT_MALE,
,U$23,Adafruit PiTFT+ 2.8in-import-fps:ADAFRUIT_TEXT_20MM,
,U$42,Adafruit PiTFT+ 2.8in-import-fps:ADAFRUIT_TEXT_30MM,
,U$12,Adafruit PiTFT+ 2.8in-import-fps:PCBFEAT-REV-040,
,"WPJ0,WPJ1",Adafruit PiTFT+ 2.8in-import-fps:SOLDERJUMPER_CLOSEDWIRE,
0,"R15,R16,R17,R18",Adafruit PiTFT+ 2.8in-import-fps:0805-NO,C2907288
0.1uF,"C2,C3,C4",Adafruit PiTFT+ 2.8in-import-fps:0805-NO,
100,"R1,R2,R3,R4",Adafruit PiTFT+ 2.8in-import-fps:0805-NO,C17408
10K,"R6,R7",Adafruit PiTFT+ 2.8in-import-fps:0805-NO,C17414
10uF,"C1,C5",Adafruit PiTFT+ 2.8in-import-fps:0805-NO,
1N4148,"D1,D2",Adafruit PiTFT+ 2.8in-import-fps:SOD-323,
22,"R10,R11",Adafruit PiTFT+ 2.8in-import-fps:0805-NO,C2907310
3.9K,"R9,R12,R13,R14",Adafruit PiTFT+ 2.8in-import-fps:0805-NO,C2907252
APX803,IC5,Adafruit PiTFT+ 2.8in-import-fps:SOT23,
BSS138,Q2,Adafruit PiTFT+ 2.8in-import-fps:SOT23-WIDE,C52895
CAT24C32,U1,Adafruit PiTFT+ 2.8in-import-fps:SOIC8_150MIL,
DISP_LCD_240X320_50PIN_2.8IN,U$2,Adafruit PiTFT+ 2.8in-import-fps:TFT_2.83IN_240X320_50PIN,
DNP,R8,Adafruit PiTFT+ 2.8in-import-fps:0805-NO,
"FIDUCIAL""""","U$10,U$11,U$18",Adafruit PiTFT+ 2.8in-import-fps:FIDUCIAL_1MM,
RASPBERRYPI_BPLUS_SHIELD_NODIM,RPI1,Adafruit PiTFT+ 2.8in-import-fps:RASPBERRYPI_BPLUS_SHIELD_NODIM,
STMPE811,U2,Adafruit PiTFT+ 2.8in-import-fps:QFN16_3MM,
